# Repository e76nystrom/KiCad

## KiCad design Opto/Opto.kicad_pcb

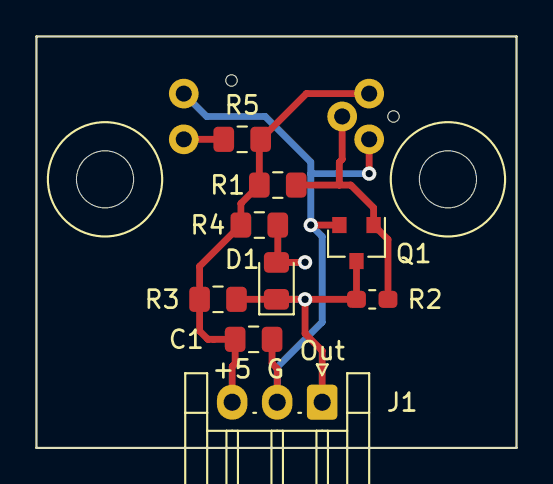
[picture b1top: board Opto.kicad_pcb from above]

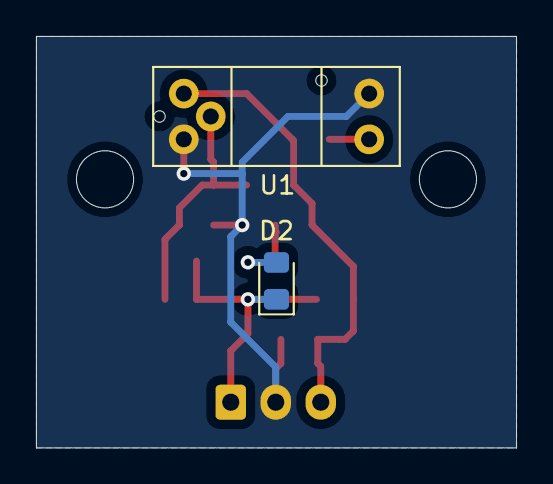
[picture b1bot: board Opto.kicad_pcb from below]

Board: 2 copper layers, 26.7 x 22.9 mm, 13 parts (2 on the bottom side), 6 nets.

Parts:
C1: C; C_0805_2012Metric_Pad1.15x1.40mm_HandSolder
D1, D2: LED; LED_0805_2012Metric_Pad1.15x1.40mm_HandSolder
H1, H2: MountingHole; MountingHole _1-8_1-4
J1: Conn_01x03; JST_EH_S3B-EH_1x03_P2.50mm_Horizontal
Q1: Q_NMOS_GSD; SOT-23
R1, R3, R4, R5: R; R_0805_2012Metric_Pad1.15x1.40mm_HandSolder
R2: R; R_0603_1608Metric_Pad1.05x0.95mm_HandSolder
U1: OptoGP1A58HRJ00F

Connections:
+5V: C1.1, J1.3, R1.1, R3.1, R4.1, R5.1, U1.3
/IntA: R5.2, U1.1
/Led+: D1.2, D2.2, R4.2
/Out: D1.1, D2.1, J1.1, Q1.3, R2.1, R3.2
/SensorOut: Q1.1, R1.2, R2.2, U1.4
GND: C1.2, J1.2, Q1.2, U1.2, U1.5

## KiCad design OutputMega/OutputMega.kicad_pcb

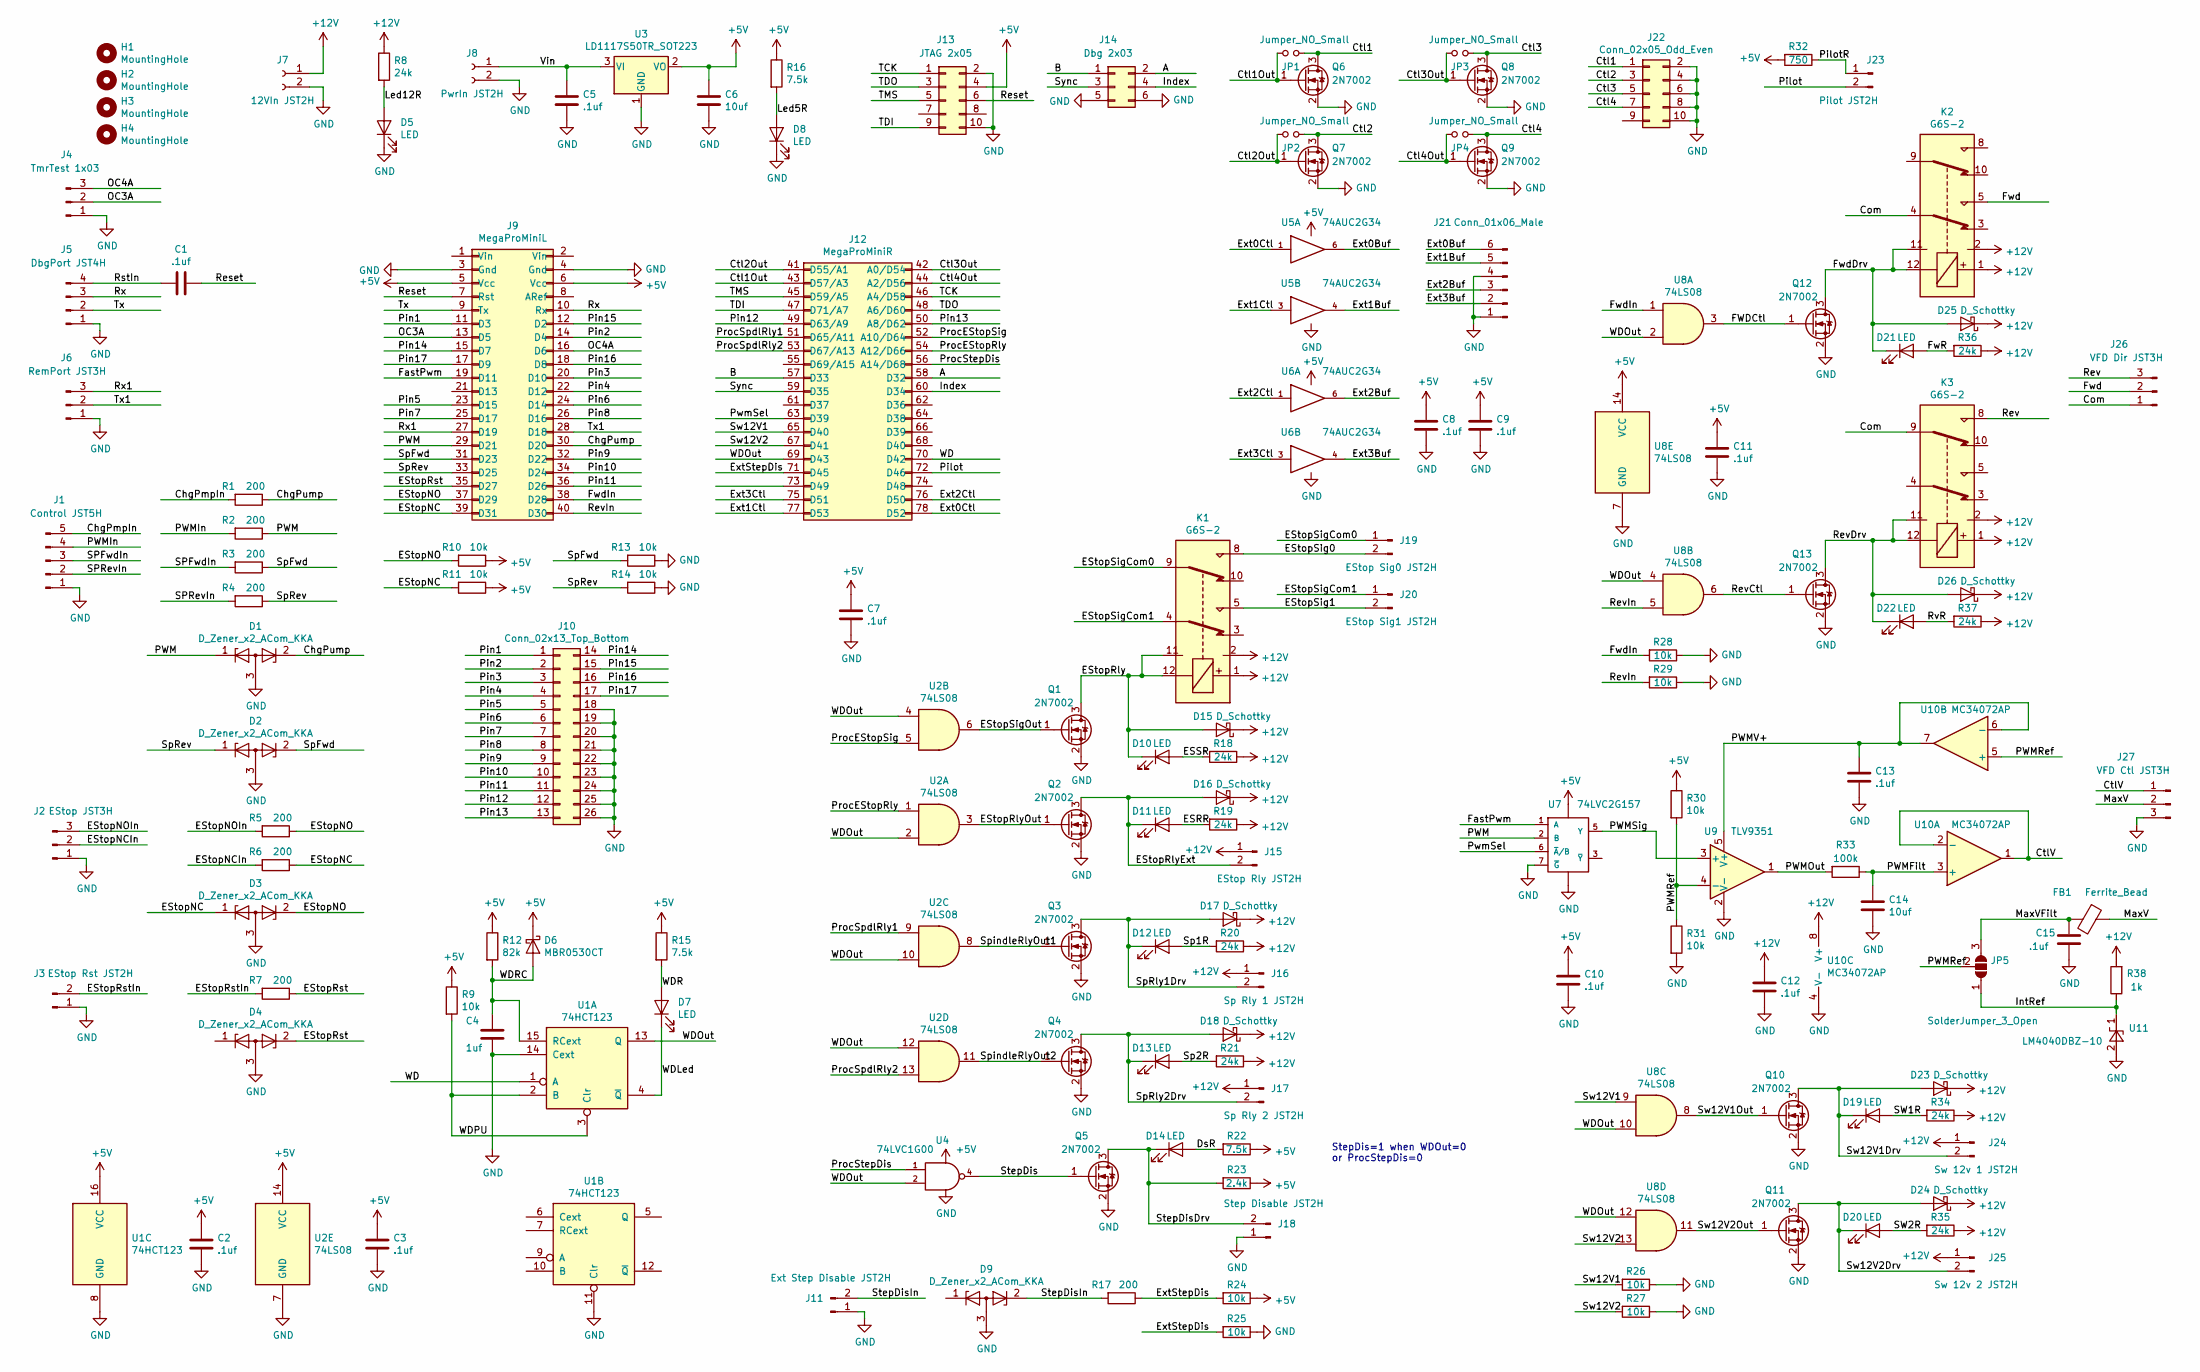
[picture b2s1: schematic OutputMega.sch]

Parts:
C1, C2, C3, C5, C7, C8, C9, C10, C11, C12, C13, C15: .1uf; C_0805_2012Metric_Pad1.15x1.40mm_HandSolder
C4: 1uf; C_0805_2012Metric_Pad1.15x1.40mm_HandSolder
C6, C14: 10uf; C_0805_2012Metric_Pad1.15x1.40mm_HandSolder
D1, D2, D3, D4, D9: D_Zener_x2_ACom_KKA; SOT-23-Handsoldering
D5, D7, D8, D10, D11, D12, D13, D14, D19, D20, D21, D22: LED; LED_0805_2012Metric_Pad1.15x1.40mm_HandSolder
D6: MBR0530CT; D_SOD-123
D15, D16, D17, D18, D23, D24, D25, D26: D_Schottky; D_SMA_Handsoldering
FB1: Ferrite_Bead; L_0805_2012Metric_Pad1.15x1.40mm_HandSolder
H1, H2, H3, H4: MountingHole; MountingHole _1-8_1-4
J1: Control JST5H; JST_EH_S5B-EH_1x05_P2.50mm_Horizontal
J2: EStop JST3H; JST_EH_S3B-EH_1x03_P2.50mm_Horizontal
J3: EStop Rst JST2H; JST_EH_S2B-EH_1x02_P2.50mm_Horizontal
J4: TmrTest 1x03; PinHeader_1x03_P2.54mm_Vertical
J5: DbgPort JST4H; JST_EH_S4B-EH_1x04_P2.50mm_Horizontal
J6: RemPort JST3H; JST_EH_S3B-EH_1x03_P2.50mm_Horizontal
J7: 12VIn JST2H; JST_EH_S2B-EH_1x02_P2.50mm_Horizontal
J8: PwrIn JST2H; JST_EH_S2B-EH_1x02_P2.50mm_Horizontal
J9: MegaProMiniL
J10: Conn_02x13_Top_Bottom; PinHeader_2x13_P2.54mm_Vertical
J11: Ext Step Disable JST2H; JST_EH_S2B-EH_1x02_P2.50mm_Horizontal
J12: MegaProMiniR
J13: JTAG 2x05; PinHeader_2x05_P2.54mm_Vertical
J14: Dbg 2x03; PinHeader_2x03_P2.54mm_Vertical
J15: EStop Rly JST2H; JST_EH_S2B-EH_1x02_P2.50mm_Horizontal
J16: Sp Rly 1 JST2H; JST_EH_S2B-EH_1x02_P2.50mm_Horizontal
J17: Sp Rly 2 JST2H; JST_EH_S2B-EH_1x02_P2.50mm_Horizontal
J18: Step Disable JST2H; JST_EH_S2B-EH_1x02_P2.50mm_Horizontal
J19: EStop Sig0 JST2H; JST_EH_S2B-EH_1x02_P2.50mm_Horizontal
J20: EStop Sig1 JST2H; JST_EH_S2B-EH_1x02_P2.50mm_Horizontal
J21: Conn_01x06_Male; JST_EH_S6B-EH_1x06_P2.50mm_Horizontal
J22: Conn_02x05_Odd_Even; PinHeader_2x05_P2.54mm_Vertical
J23: Pilot JST2H; JST_EH_S2B-EH_1x02_P2.50mm_Horizontal
J24: Sw 12v 1 JST2H; JST_EH_S2B-EH_1x02_P2.50mm_Horizontal
J25: Sw 12v 2 JST2H; JST_EH_S2B-EH_1x02_P2.50mm_Horizontal
J26: VFD Dir JST3H; JST_EH_S3B-EH_1x03_P2.50mm_Horizontal
J27: VFD Ctl JST3H; JST_EH_S3B-EH_1x03_P2.50mm_Horizontal
JP1, JP2, JP3, JP4: Jumper_NO_Small; R_0603_1608Metric_Pad1.05x0.95mm_HandSolder
JP5: SolderJumper_3_Open; Jumper_0603_3
K1, K2, K3: G6S-2; Relay_DPDT_Omron_G6S-2
Q1, Q2, Q3, Q4, Q5, Q6, Q7, Q8, Q9, Q10, Q11, Q12, Q13: 2N7002; SOT-23-Handsoldering
R1, R2, R3, R4, R5, R6, R7, R17: 200; R_0805_2012Metric_Pad1.15x1.40mm_HandSolder
R8, R18, R19, R20, R21, R34, R35, R36, R37: 24k; R_0805_2012Metric_Pad1.15x1.40mm_HandSolder
R9, R10, R11, R13, R14, R24, R25, R26, R27, R28, R29, R30, R31: 10k; R_0805_2012Metric_Pad1.15x1.40mm_HandSolder
R12: 82k; R_0805_2012Metric_Pad1.15x1.40mm_HandSolder
R15, R16, R22: 7.5k; R_0805_2012Metric_Pad1.15x1.40mm_HandSolder
R23: 2.4k; R_0805_2012Metric_Pad1.15x1.40mm_HandSolder
R32: 750; R_0805_2012Metric_Pad1.15x1.40mm_HandSolder
R33: 100k; R_0805_2012Metric_Pad1.15x1.40mm_HandSolder
R38: 1k; R_0805_2012Metric_Pad1.15x1.40mm_HandSolder
U1: 74HCT123; SOIC-16_3.9x9.9mm_P1.27mm
U2, U8: 74LS08; SOIC-14_3.9x8.7mm_P1.27mm
U3: LD1117S50TR_SOT223; SOT-223-3_TabPin2
U4: 74LVC1G00; SOT-23-5
U5, U6: 74AUC2G34; SOT-23-6_Handsoldering
U7: 74LVC2G157; TSSOP-8_3x3mm_P0.65mm
U9: TLV9351; SOT-23-5
U10: MC34072AP; SOIC-8_3.9x4.9mm_P1.27mm
U11: LM4040DBZ-10; SOT-23-Handsoldering

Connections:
+5V: C2.1, C3.1, C6.1, C7.1, C8.1, C9.1, C10.1, C11.1, D6.1 (K), J9.5 (Vcc), J9.6 (Vcc), J13.4, R9.1, R10.1, R11.1, R12.1, R15.1, R16.1, R22.1, R23.1, R24.1, R30.1, R32.2, U1.16 (VCC), U2.14 (VCC), U3.2 (VO), U4.5 (VCC), U5.5 (VCC), U6.5 (VCC), U7.8 (VCC), U8.14 (VCC)
+12V: C12.1, D15.1 (K), D16.1 (K), D17.1 (K), D18.1 (K), D23.1 (K), D24.1 (K), D25.1 (K), D26.1 (K), J7.1, J15.1, J16.1, J17.1, J24.1, J25.1, K1.1, K1.2, K2.1, K2.2, K3.1, K3.2, R8.1, R18.1, R19.1, R20.1, R21.1, R34.1, R35.1, R36.1, R37.1, R38.2, U10.8 (V+)
/A: J12.58 (D32), J14.2
/B: J12.57 (D33), J14.1
/ChgPmpIn: J1.5, R1.2
/ChgPump: D1.2 (K), J9.30 (D20), R1.1
/Com: J26.1, K2.4, K3.9
/Ctl1: J22.1, JP1.2, Q6.3 (D)
/Ctl1Out: J12.43 (D57/A3), JP1.1, Q6.1 (G)
/Ctl2: J22.3, JP2.2, Q7.3 (D)
/Ctl2Out: J12.41 (D55/A1), JP2.1, Q7.1 (G)
/Ctl3: J22.5, JP3.2, Q8.3 (D)
/Ctl3Out: J12.42 (A0/D54), JP3.1, Q8.1 (G)
/Ctl4: J22.7, JP4.2, Q9.3 (D)
/Ctl4Out: J12.44 (A2/D56), JP4.1, Q9.1 (G)
/CtlV: J27.1, U10.1, U10.2 (-)
/DsR: D14.2 (A), R22.2
/ESRR: D11.2 (A), R19.2
/ESSR: D10.2 (A), R18.2
/EStopNC: D3.1 (K), J9.39 (D31), R6.1, R11.2
/EStopNCIn: J2.2, R6.2
/EStopNO: D3.2 (K), J9.37 (D29), R5.1, R10.2
/EStopNOIn: J2.3, R5.2
/EStopRly: D10.1 (K), D15.2 (A), K1.11, K1.12, Q1.3 (D)
/EStopRlyExt: D11.1 (K), D16.2 (A), J15.2, Q2.3 (D)
/EStopRlyOut: Q2.1 (G), U2.3
/EStopRst: D4.2 (K), J9.35 (D27), R7.1
/EStopRstIn: J3.2, R7.2
/EStopSig0: J19.2, K1.8
/EStopSig1: J20.2, K1.5
/EStopSigCom0: J19.1, K1.9
/EStopSigCom1: J20.1, K1.4
/EStopSigOut: Q1.1 (G), U2.6
/Ext0Buf: J21.6, U5.6
/Ext0Ctl: J12.78 (D52), U5.1
/Ext1Buf: J21.5, U5.4
/Ext1Ctl: J12.77 (D53), U5.3
/Ext2Buf: J21.3, U6.6
/Ext2Ctl: J12.76 (D50), U6.1
/Ext3Buf: J21.2, U6.4
/Ext3Ctl: J12.75 (D51), U6.3
/ExtStepDis: J12.71 (D45), R17.1, R24.2, R25.2
/FWDCtl: Q12.1 (G), U8.3
/FastPwm: J9.19 (D11), U7.1 (A)
/FwR: D21.2 (A), R36.2
/Fwd: J26.2, K2.5
/FwdDrv: D21.1 (K), D25.2 (A), K2.11, K2.12, Q12.3 (D)
/FwdIn: J9.38 (D28), R28.2, U8.1
/Index: J12.60 (D34), J14.4
/IntRef: JP5.1 (A), R38.1, U11.1 (K)
/Led5R: D8.2 (A), R16.2
/Led12R: D5.2 (A), R8.2
/MaxV: FB1.1, J27.2
/MaxVFilt: C15.1, FB1.2, JP5.3 (B)
/OC3A: J4.2, J9.13 (D5)
/OC4A: J4.3, J9.16 (D6)
/PWM: D1.1 (K), J9.29 (D21), R2.1, U7.2 (B)
/PWMFilt: C14.1, R33.1, U10.3 (+)
/PWMIn: J1.4, R2.2
/PWMOut: R33.2, U9.1
/PWMRef: JP5.2 (C), R30.2, R31.1, U9.4 (-), U10.5 (+)
/PWMSig: U7.5 (Y), U9.3 (+)
/PWMV+: C13.1, U9.5 (V+), U10.6 (-), U10.7
/Pilot: J12.72 (D46), J23.2
/PilotR: J23.1, R32.1
/Pin1: J9.11 (D3), J10.1
/Pin2: J9.14 (D4), J10.2
/Pin3: J9.20 (D10), J10.3
/Pin4: J9.22 (D12), J10.4
/Pin5: J9.23 (D15), J10.5
/Pin6: J9.24 (D14), J10.6
/Pin7: J9.25 (D17), J10.7
/Pin8: J9.26 (D16), J10.8
/Pin9: J9.32 (D22), J10.9
/Pin10: J9.34 (D24), J10.10
/Pin11: J9.36 (D26), J10.11
/Pin12: J10.12, J12.49 (D63/A9)
/Pin13: J10.13, J12.50 (A8/D62)
/Pin14: J9.15 (D7), J10.14
/Pin15: J9.12 (D2), J10.15
/Pin16: J9.18 (D8), J10.16
/Pin17: J9.17 (D9), J10.17
/ProcEStopRly: J12.54 (A12/D66), U2.1
/ProcEStopSig: J12.52 (A10/D64), U2.5
/ProcSpdlRly1: J12.51 (D65/A11), U2.9
/ProcSpdlRly2: J12.53 (D67/A13), U2.13
/ProcStepDis: J12.56 (A14/D68), U4.1
/PwmSel: J12.63 (D39), U7.6 (~A~/B)
/Reset: C1.1, J9.7 (Rst), J13.6
/Rev: J26.3, K3.8
/RevCtl: Q13.1 (G), U8.6
/RevDrv: D22.1 (K), D26.2 (A), K3.11, K3.12, Q13.3 (D)
/RevIn: J9.40 (D30), R29.2, U8.5
/RstIn: C1.2, J5.4
/RvR: D22.2 (A), R37.2
/Rx: J5.3, J9.10 (Rx)
/Rx1: J6.3, J9.27 (D19)
/SPFwdIn: J1.3, R3.2
/SPRevIn: J1.2, R4.2
/SW1R: D19.2 (A), R34.2
/SW2R: D20.2 (A), R35.2
/Sp1R: D12.2 (A), R20.2
/Sp2R: D13.2 (A), R21.2
/SpFwd: D2.2 (K), J9.31 (D23), R3.1, R13.2
/SpRev: D2.1 (K), J9.33 (D25), R4.1, R14.2
/SpRly1Drv: D12.1 (K), D17.2 (A), J16.2, Q3.3 (D)
/SpRly2Drv: D13.1 (K), D18.2 (A), J17.2, Q4.3 (D)
/SpindleRlyOut1: Q3.1 (G), U2.8
/SpindleRlyOut2: Q4.1 (G), U2.11
/StepDis: Q5.1 (G), U4.4
/StepDisDrv: D14.1 (K), J18.2, Q5.3 (D), R23.2
/StepDisIn: D9.2 (K), J11.2, R17.2
/Sw12V1: J12.65 (D40), R26.2, U8.9
/Sw12V1Drv: D19.1 (K), D23.2 (A), J24.2, Q10.3 (D)
/Sw12V1Out: Q10.1 (G), U8.8
/Sw12V2: J12.67 (D41), R27.2, U8.13
/Sw12V2Drv: D20.1 (K), D24.2 (A), J25.2, Q11.3 (D)
/Sw12V2Out: Q11.1 (G), U8.11
/Sync: J12.59 (D35), J14.3
/TCK: J12.46 (A4/D58), J13.1
/TDI: J12.47 (D71/A7), J13.9
/TDO: J12.48 (A6/D60), J13.3
/TMS: J12.45 (D59/A5), J13.5
/Tx: J5.2, J9.9 (Tx)
/Tx1: J6.2, J9.28 (D18)
/Vin: C5.1, J8.1, U3.3 (VI)
/WD: J12.70 (D42), U1.1 (A)
/WDLed: D7.1 (K), U1.4 (~Q)
/WDOut: J12.69 (D43), U1.13 (Q), U2.2, U2.4, U2.10, U2.12, U4.2, U8.2, U8.4, U8.10, U8.12
/WDPU: R9.2, U1.2 (B), U1.3 (Clr)
/WDR: D7.2 (A), R15.2
/WDRC: C4.1, D6.2 (A), R12.2, U1.15 (RCext)
GND: C2.2, C3.2, C4.2, C5.2, C6.2, C7.2, C8.2, C9.2, C10.2, C11.2, C12.2, C13.2, C14.2, C15.2, D1.3 (A), D2.3 (A), D3.3 (A), D4.3 (A), D5.1 (K), D8.1 (K), D9.3 (A), J1.1, J2.1, J3.1, J4.1, J5.1, J6.1, J7.2, J8.2, J9.3 (Gnd), J9.4 (Gnd), J10.18, J10.19, J10.20, J10.21, J10.22, J10.23, J10.24, J10.25, J10.26, J11.1, J13.2, J13.10, J14.5, J14.6, J18.1, J21.1, J21.4, J22.2, J22.4, J22.6, J22.8, J22.10, J27.3, Q1.2 (S), Q2.2 (S), Q3.2 (S), Q4.2 (S), Q5.2 (S), Q6.2 (S), Q7.2 (S), Q8.2 (S), Q9.2 (S), Q10.2 (S), Q11.2 (S), Q12.2 (S), Q13.2 (S), R13.1, R14.1, R25.1, R26.1, R27.1, R28.1, R29.1, R31.2, U1.8 (GND), U1.11 (Clr), U1.14 (Cext), U2.7 (GND), U3.1 (GND), U4.3 (GND), U5.2 (GND), U6.2 (GND), U7.4 (GND), U7.7 (~G), U8.7 (GND), U9.2 (V-), U10.4 (V-), U11.2 (A)

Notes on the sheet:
StepDis=1 when WDOut=0 or ProcStepDis=0

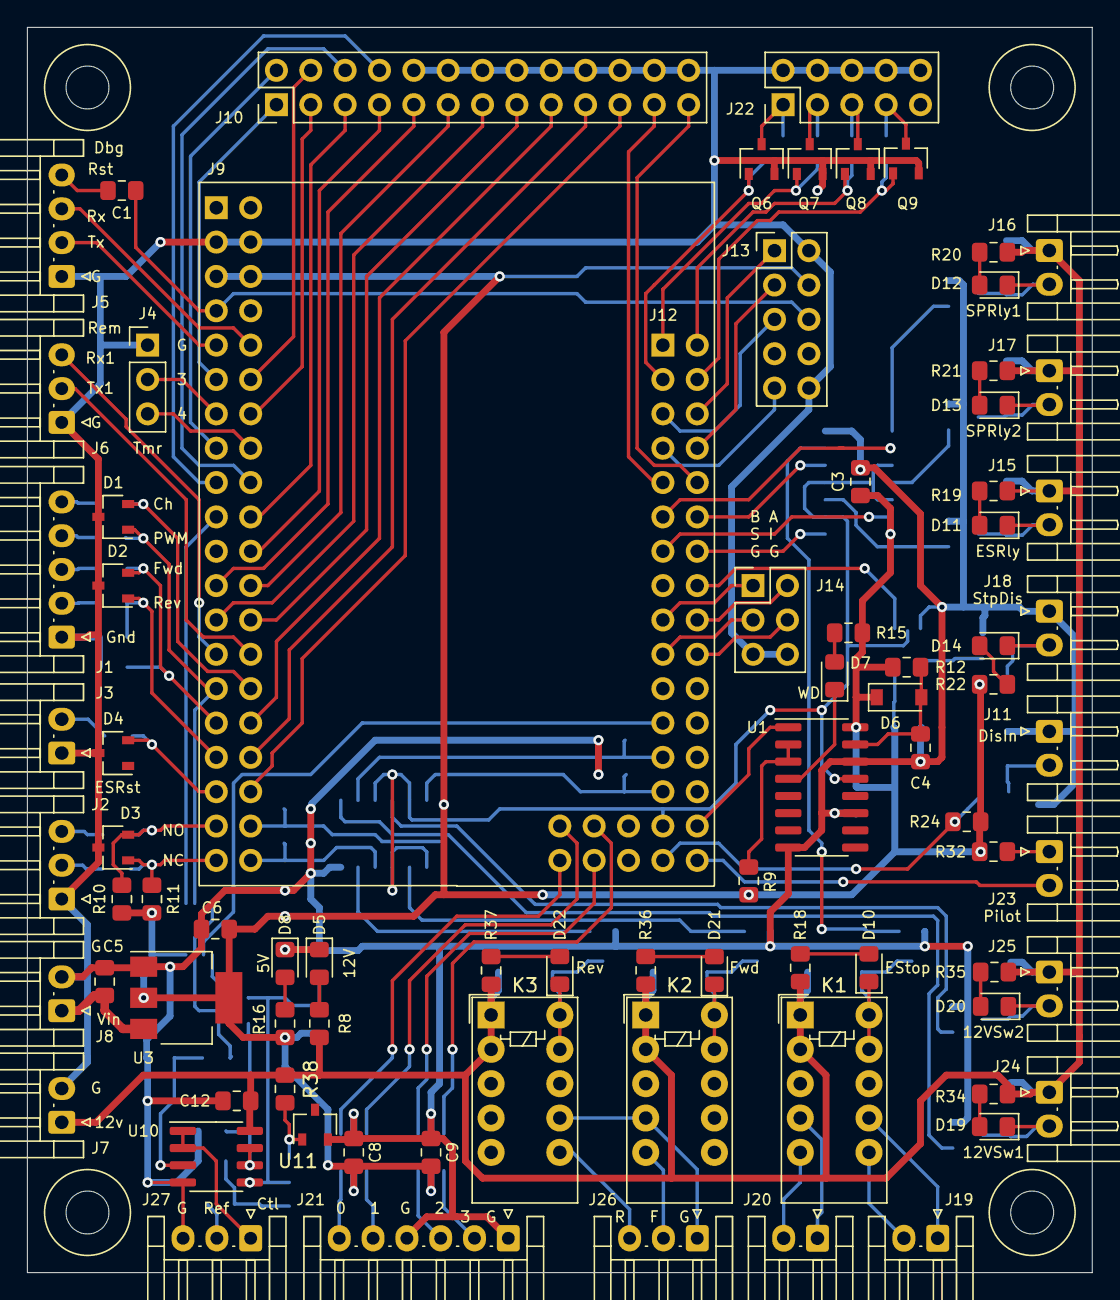
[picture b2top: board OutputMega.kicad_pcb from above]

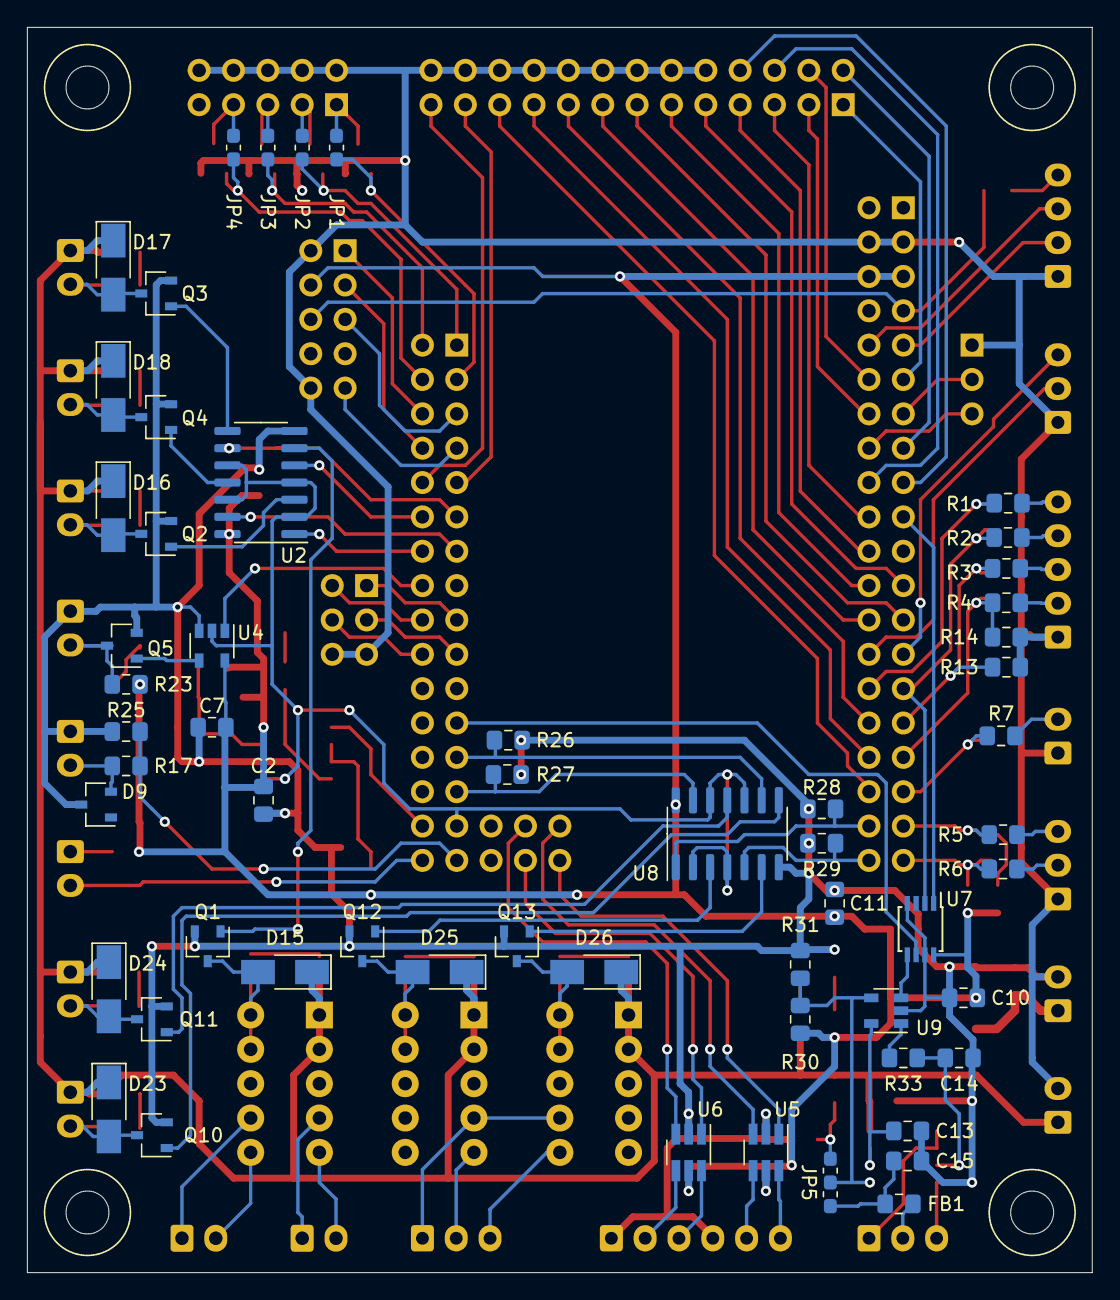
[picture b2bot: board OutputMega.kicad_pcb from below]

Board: 2 copper layers, 78.7 x 92.1 mm, 143 parts (57 on the bottom side), 133 nets.

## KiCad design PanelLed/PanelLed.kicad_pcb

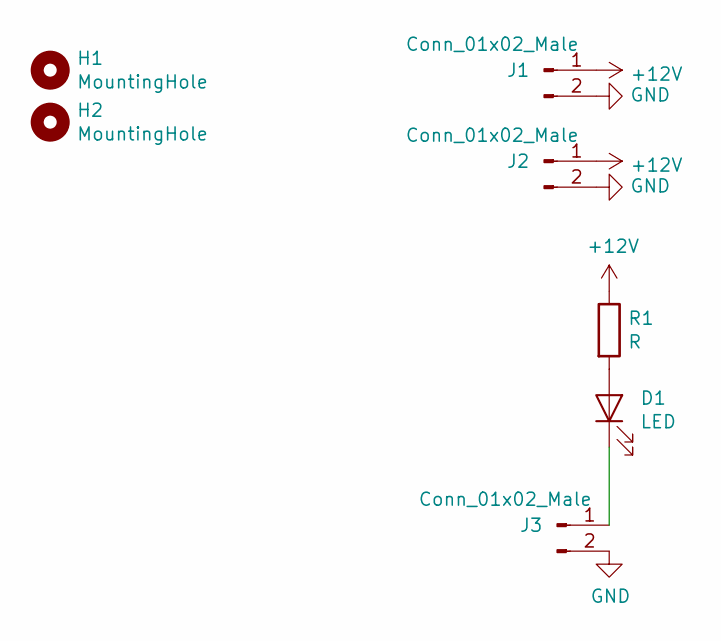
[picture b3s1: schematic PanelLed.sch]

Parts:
D1: LED; LED_D5.0mm
H1, H2: MountingHole; MountingHole _1-8_1-4
J1, J2, J3: Conn_01x02_Male; JST_EH_B2B-EH-A_1x02_P2.50mm_Vertical
R1: R; R_0805_2012Metric_Pad1.15x1.40mm_HandSolder

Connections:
+12V: J1.1, J2.1, R1.1
GND: J1.2, J2.2, J3.2
unnamed: D1.1 (K), J3.1
unnamed: D1.2 (A), R1.2

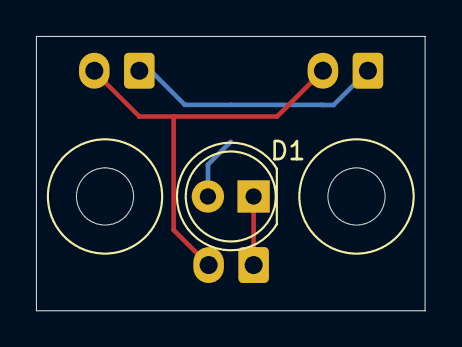
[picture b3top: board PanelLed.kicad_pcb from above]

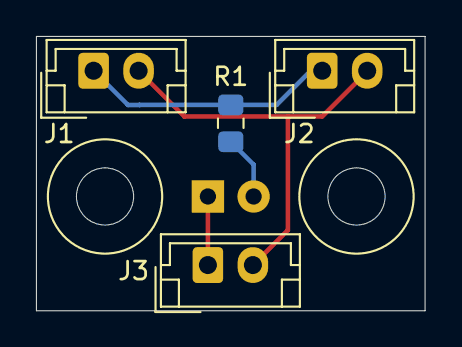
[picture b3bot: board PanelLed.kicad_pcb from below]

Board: 2 copper layers, 21.6 x 15.2 mm, 7 parts (4 on the bottom side), 4 nets.

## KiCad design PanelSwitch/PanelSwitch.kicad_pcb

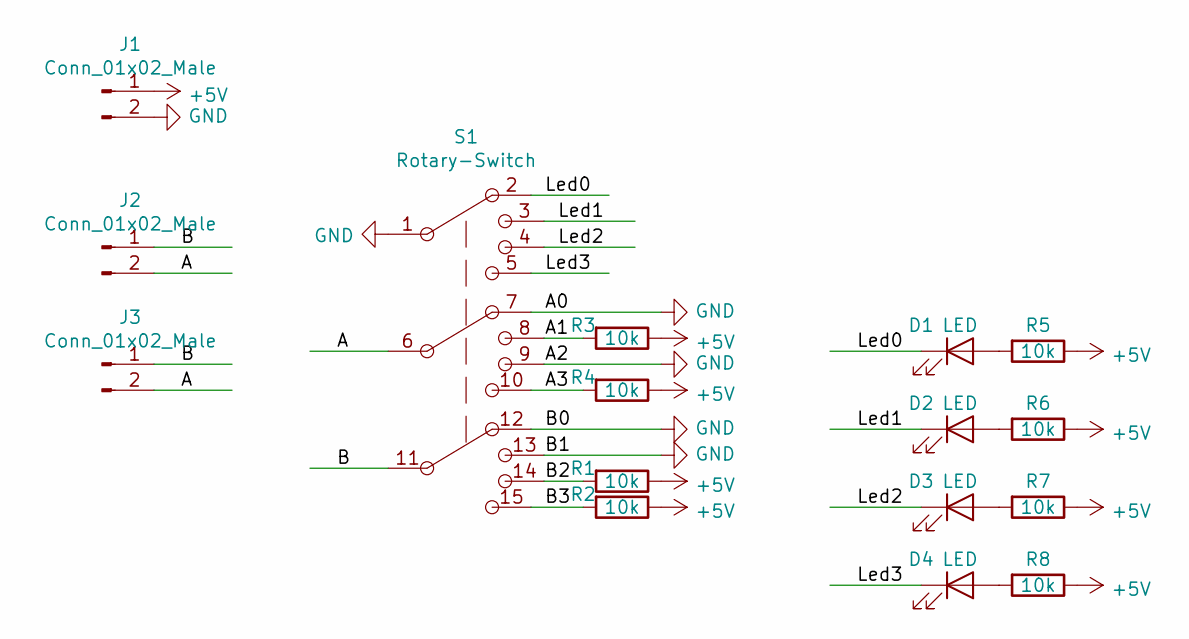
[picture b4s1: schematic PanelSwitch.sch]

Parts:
D1, D2, D3, D4: LED; LED_D5.0mm
J1, J2, J3: Conn_01x02_Male; JST_EH_B2B-EH-A_1x02_P2.50mm_Vertical
R1, R2, R3, R4, R5, R6, R7, R8: 10k; R_0805_2012Metric_Pad1.15x1.40mm_HandSolder
S1: Rotary-Switch

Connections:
+5V: J1.1, R1.1, R2.1, R3.1, R4.1, R5.1, R6.1, R7.1, R8.1
/A: J2.2, J3.2, S1.6
/A1: R3.2, S1.8
/A3: R4.2, S1.10
/B: J2.1, J3.1, S1.11
/B2: R1.2, S1.14
/B3: R2.2, S1.15
/Led0: D1.1 (K), S1.2
/Led1: D2.1 (K), S1.3
/Led2: D3.1 (K), S1.4
/Led3: D4.1 (K), S1.5
GND: J1.2, S1.1, S1.7, S1.9, S1.12, S1.13
unnamed: D1.2 (A), R5.2
unnamed: D2.2 (A), R6.2
unnamed: D3.2 (A), R7.2
unnamed: D4.2 (A), R8.2

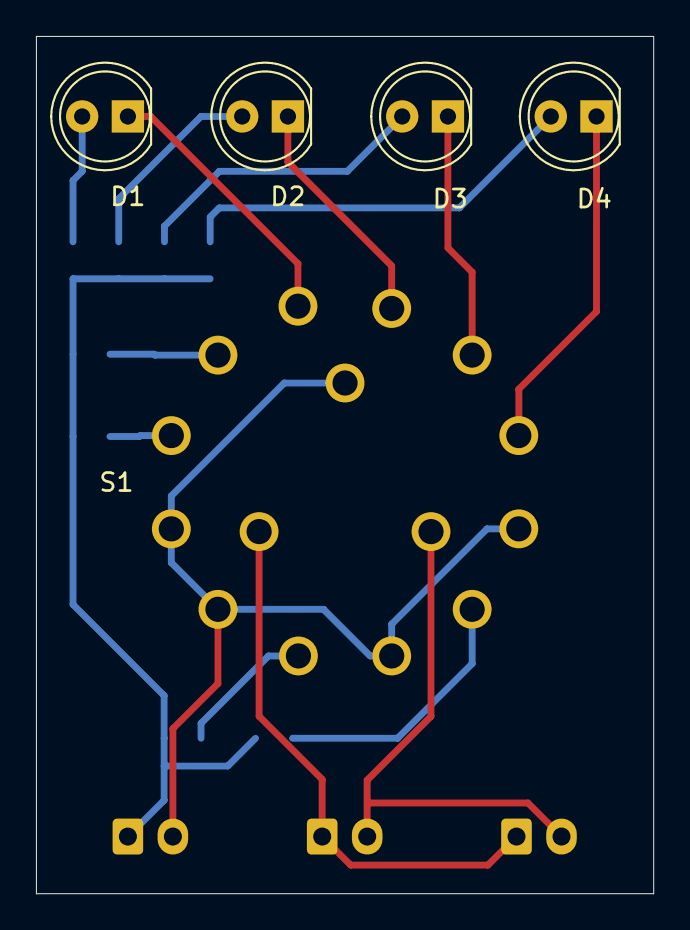
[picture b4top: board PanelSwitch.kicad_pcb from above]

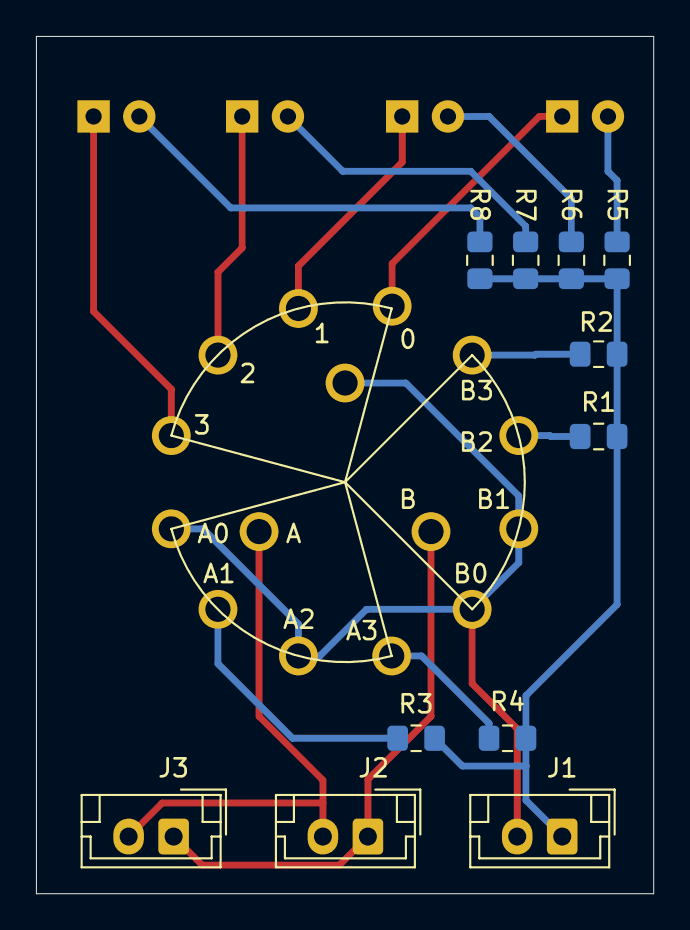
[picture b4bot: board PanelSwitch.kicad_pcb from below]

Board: 2 copper layers, 34.3 x 47.6 mm, 16 parts (11 on the bottom side), 16 nets.

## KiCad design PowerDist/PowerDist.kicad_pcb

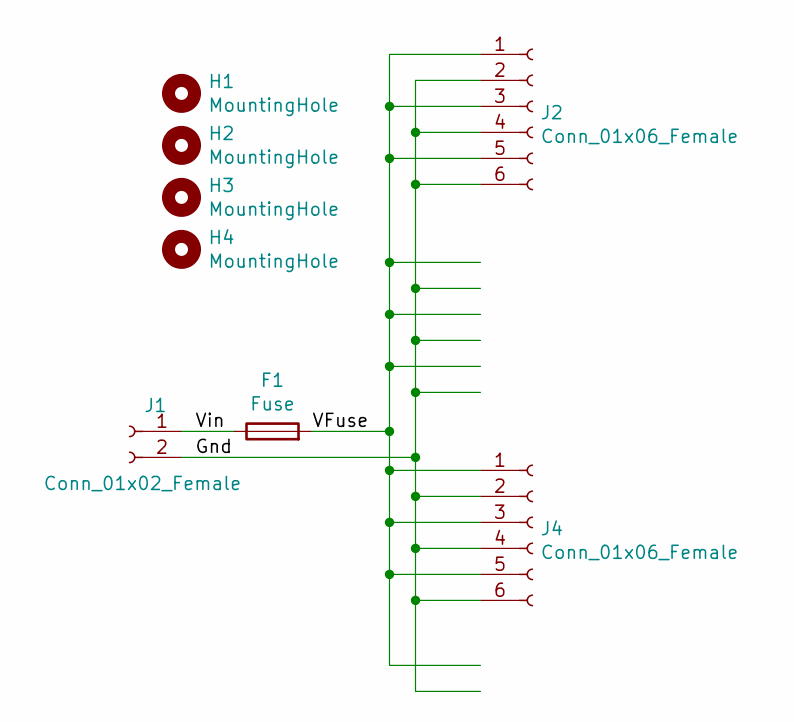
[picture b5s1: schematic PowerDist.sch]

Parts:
F1: Fuse; Fuse_Holder
H1, H2, H3, H4: MountingHole; MountingHole _1-8_1-4
J1: Conn_01x02_Female; PhoenixContact_MC_1,5_2-G-3.81_1x02_P3.81mm_Horizontal
J2, J4: Conn_01x06_Female; PhoenixContact_MCV_1,5_6-G-3.81_1x06_P3.81mm_Vertical

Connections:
/Gnd: J1.2, J2.2, J2.4, J2.6, J4.2, J4.4, J4.6
/VFuse: F1.2, J2.1, J2.3, J2.5, J4.1, J4.3, J4.5
/Vin: F1.1, J1.1

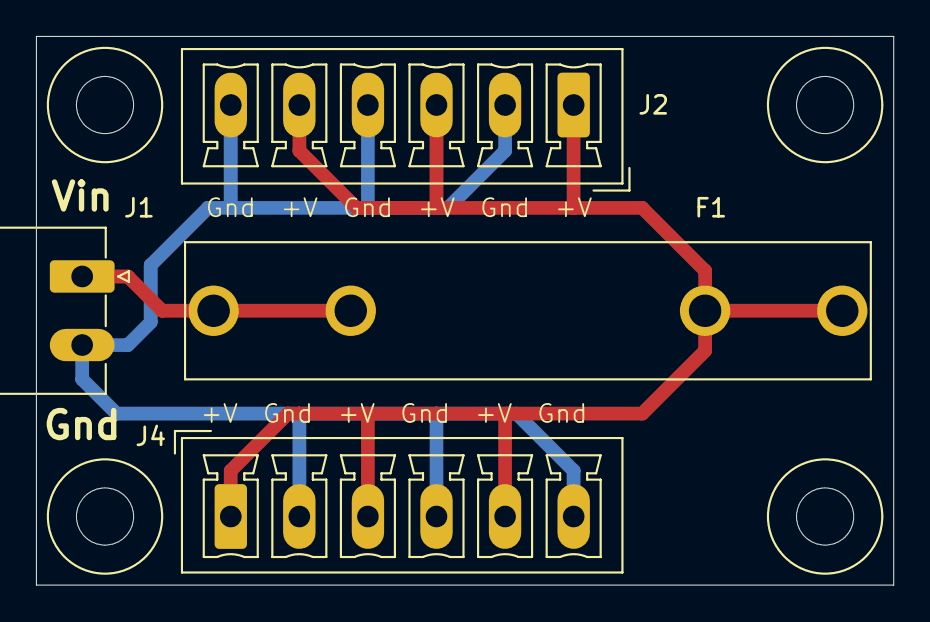
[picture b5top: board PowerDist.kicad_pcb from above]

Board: 2 copper layers, 47.6 x 30.5 mm, 8 parts (0 on the bottom side), 3 nets.

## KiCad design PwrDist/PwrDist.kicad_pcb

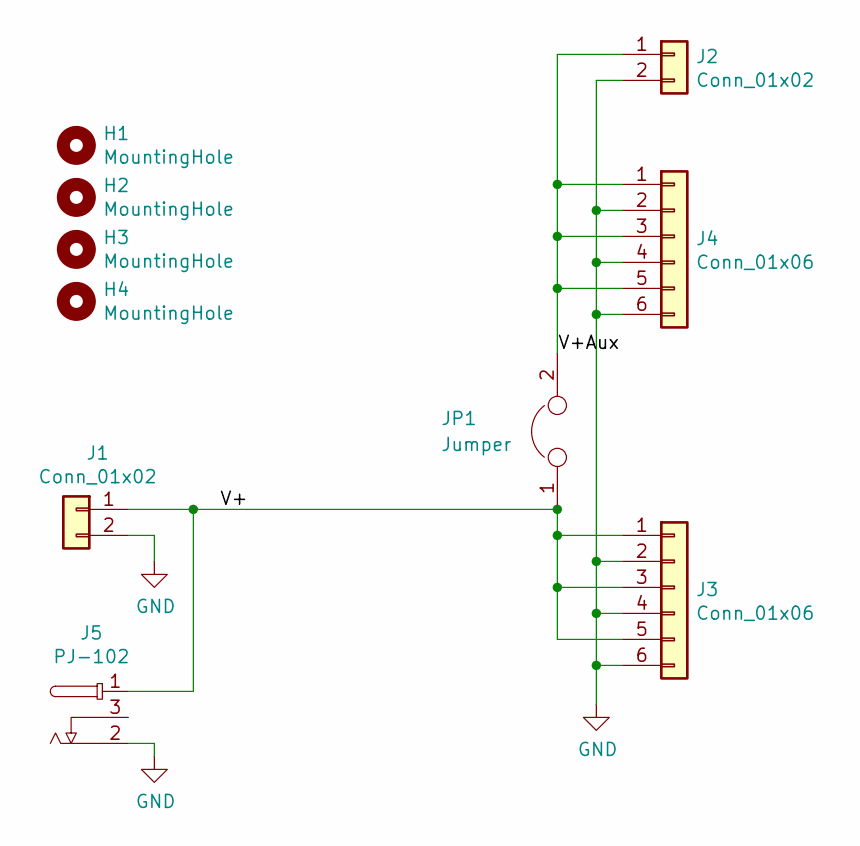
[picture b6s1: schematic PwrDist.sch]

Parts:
H1, H2, H3, H4: MountingHole; MountingHole _1-8_1-4
J1, J2: Conn_01x02; 2 Pin 3.81mm
J3, J4: Conn_01x06; 6_Pin_3.81mm
J5: PJ-102
JP1: Jumper; R_1210_3225Metric_Pad1.42x2.65mm_HandSolder

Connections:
/V+: J1.1, J3.1, J3.3, J3.5, J5.1, JP1.1
/V+Aux: J2.1, J4.1, J4.3, J4.5, JP1.2
GND: J1.2, J2.2, J3.2, J3.4, J3.6, J4.2, J4.4, J4.6, J5.2

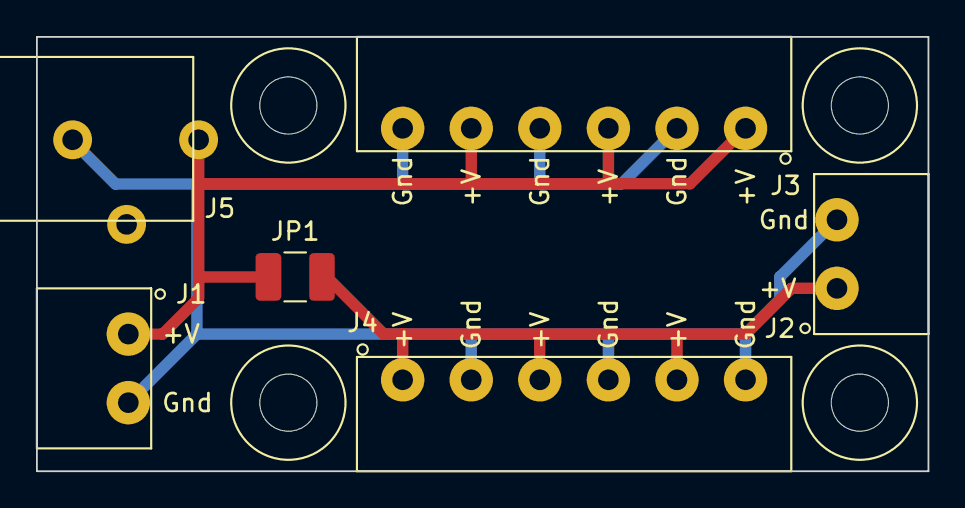
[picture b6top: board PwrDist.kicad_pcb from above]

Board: 2 copper layers, 49.5 x 24.1 mm, 10 parts (0 on the bottom side), 3 nets.
